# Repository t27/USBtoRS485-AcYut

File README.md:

#USB to RS485 Converter

This is a board which converts USB signals to RS485 signals. The connectors are included so as to make it easier to use for the Robotis Dynamixel motors.

Uses the FTDI FT232RL for USB to Serial and the MAX485 for Serial to RS485 conversion.

Built for Team AcYut at CRIS, BITS Pilani.

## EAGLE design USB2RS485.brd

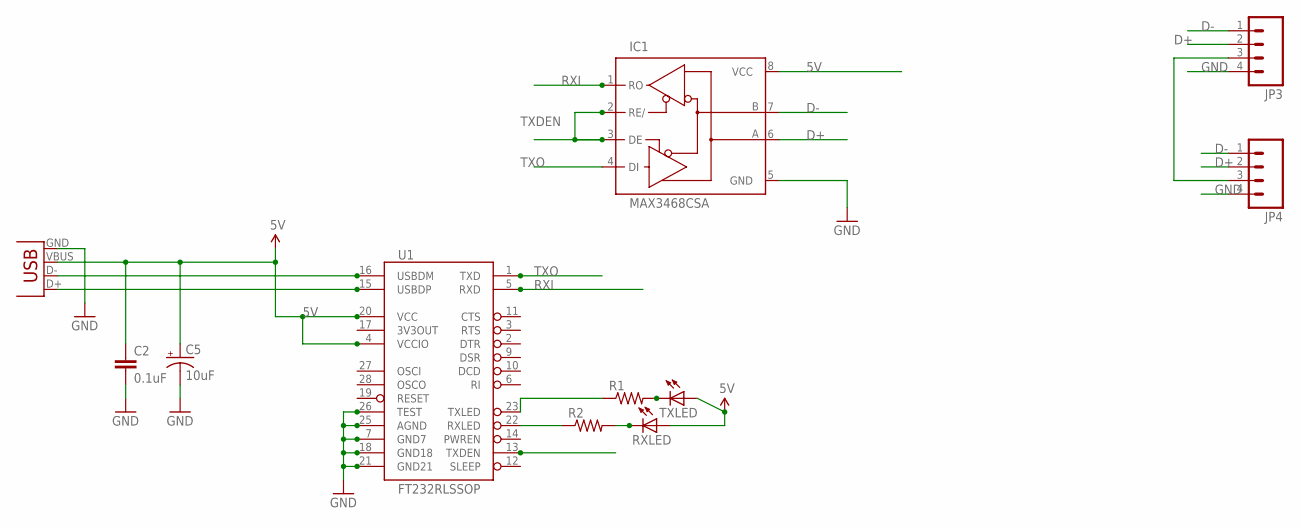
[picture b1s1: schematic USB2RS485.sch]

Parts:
C2: 0.1uF; 0402-CAP
C5: 10uF; EIA3216
IC1: MAX3468CSA; SO08
JP3, JP4: M04LOCK_LONGPADS; 1X04_LOCK_LONGPADS
R1, R2: RESISTOR0603-RES; 0603-RES
RXLED: LED0603; LED-0603
TXLED: LED0603; LED-0603
U1: FT232RLSSOP; SSOP28DB
X2: USB-SMD-NS; USB-MINIB-NOSTOP

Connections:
5V: C2.1, C5.A (+), IC1.8 (VCC), RXLED.A, TXLED.A, U1.4 (VCCIO), U1.20 (VCC), X2.VBUS
D+: IC1.6 (A), JP3.2, JP4.2
D-: IC1.7 (B), JP3.1, JP4.1
GND: C2.2, C5.C (-), IC1.5 (GND), JP3.4, JP4.4, U1.7 (GND7), U1.18 (GND18), U1.21 (GND21), U1.25 (AGND), U1.26 (TEST), X2.GND
unnamed: R1.1, U1.23 (TXLED)
unnamed: R2.1, U1.22 (RXLED)
unnamed: R1.2, TXLED.C
unnamed: JP3.3, JP4.3
unnamed: R2.2, RXLED.C
RXI: IC1.1 (RO), U1.5 (RXD)
TXDEN: IC1.2 (RE/), IC1.3 (DE), U1.13 (TXDEN)
TXO: IC1.4 (DI), U1.1 (TXD)
USB_D+: U1.15 (USBDP), X2.D+
USB_D-: U1.16 (USBDM), X2.D-

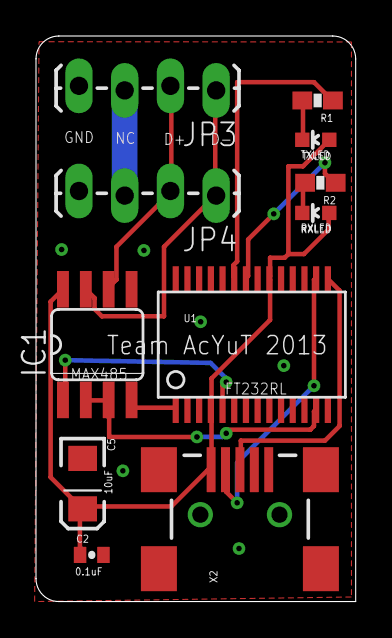
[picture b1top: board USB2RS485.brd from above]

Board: 2 copper layers, 17.8 x 31.4 mm, 11 parts (0 on the bottom side), 14 nets.

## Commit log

2015-02-11 readme update

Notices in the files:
parts and their libraries:
SparkFun-Connectors: Licensing: CC v3.0 Share-Alike You are welcome to use this library for commercial purposes.
